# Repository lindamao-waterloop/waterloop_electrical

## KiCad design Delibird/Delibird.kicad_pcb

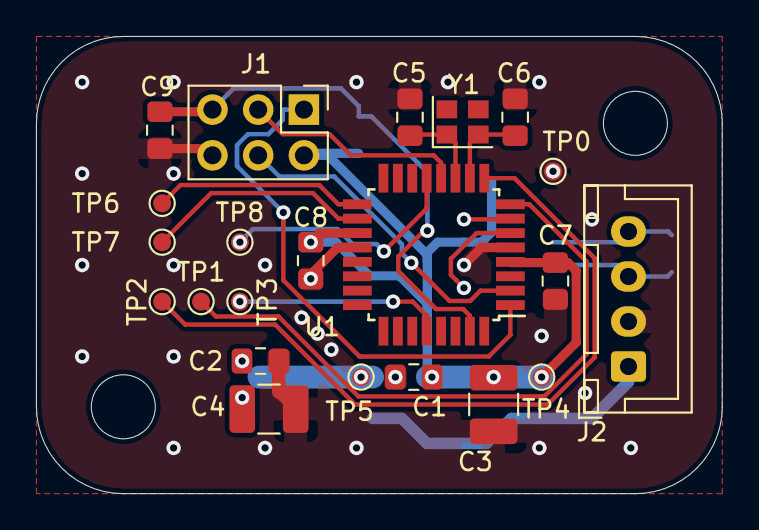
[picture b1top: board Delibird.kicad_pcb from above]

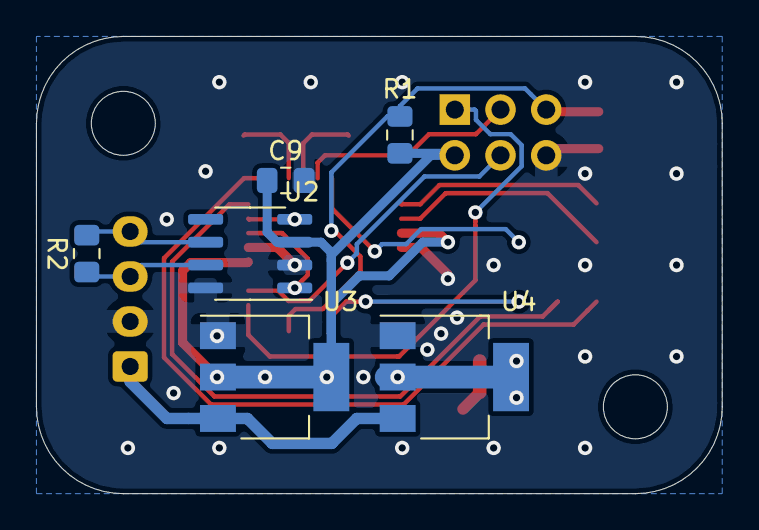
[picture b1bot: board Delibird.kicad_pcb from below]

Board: 2 copper layers, 38.1 x 25.4 mm, 28 parts (6 on the bottom side), 20 nets.

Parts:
C1, C2, C7, C9: 100n; C_0805_2012Metric_Pad1.15x1.40mm_HandSolder
C3, C4: 100u; C_1210_3225Metric_Pad1.42x2.65mm_HandSolder
C5, C6: 20p; C_0805_2012Metric_Pad1.15x1.40mm_HandSolder
C8, C9#2: 100p; C_0805_2012Metric_Pad1.15x1.40mm_HandSolder
J1: ISP-6; PinHeader_2x03_P2.54mm_Vertical
J2: Conn_01x04_Male; JST_XH_B4B-XH-A_1x04_P2.50mm_Vertical
R1: 10k; R_0805_2012Metric_Pad1.15x1.40mm_HandSolder
R2: 120; R_0805_2012Metric_Pad1.15x1.40mm_HandSolder
TP0, TP1, TP2, TP3, TP4, TP5, TP6, TP7, TP8: TestPoint; TestPoint_Pad_D1.0mm
U1: ATmega16M1-AU; TQFP-32_7x7mm_P0.8mm
U2: TJA1051T; SOIC-8_3.9x4.9mm_P1.27mm
U3: NCP1117-5V; SOT-223-3_TabPin2
U4: NCP1117-3.3V; SOT-223-3_TabPin2
Y1: Crystal; Crystal_SMD_2520-4Pin_2.5x2.0mm

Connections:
+3V3: C2.1, C4.1, TP5.1, U4.2
+5V: C1.1, C3.1, C7.1, C8.1, C9.1, J1.2, R1.1, TP4.1, U1.4, U1.19, U2.3, U3.2
/ADC2: TP8.1, U1.13
/AMP1+: TP7.1, U1.18
/AMP1-: TP6.1, U1.17
/CANRX: U1.7, U2.4
/CANTX: U1.6, U2.1
/MISO: TP1.1, U1.8
/MISO_A: J1.1, U1.1
/MOSI: TP2.1, U1.9
/MOSI_A: J1.4, U1.2
/RESET: C9#2.1, J1.5, R1.2, U1.31
/SCK: TP3.1, U1.28
/SCK_A: J1.3, U1.12
/XTAL1: C6.1, U1.10, Y1.2
/XTAL2: C5.1, U1.11, Y1.1
CANH: J2.3, R2.1, U2.7
CANL: J2.4, R2.2, U2.6
Earth: C1.2, C2.2, C3.2, C4.2, C5.2, C6.2, C7.2, C8.2, C9.2, C9#2.2, J1.6, J2.2, TP0.1, U1.5, U1.20, U2.2, U2.8, U3.1, U4.1
UIN: J2.1, U3.3, U4.3
